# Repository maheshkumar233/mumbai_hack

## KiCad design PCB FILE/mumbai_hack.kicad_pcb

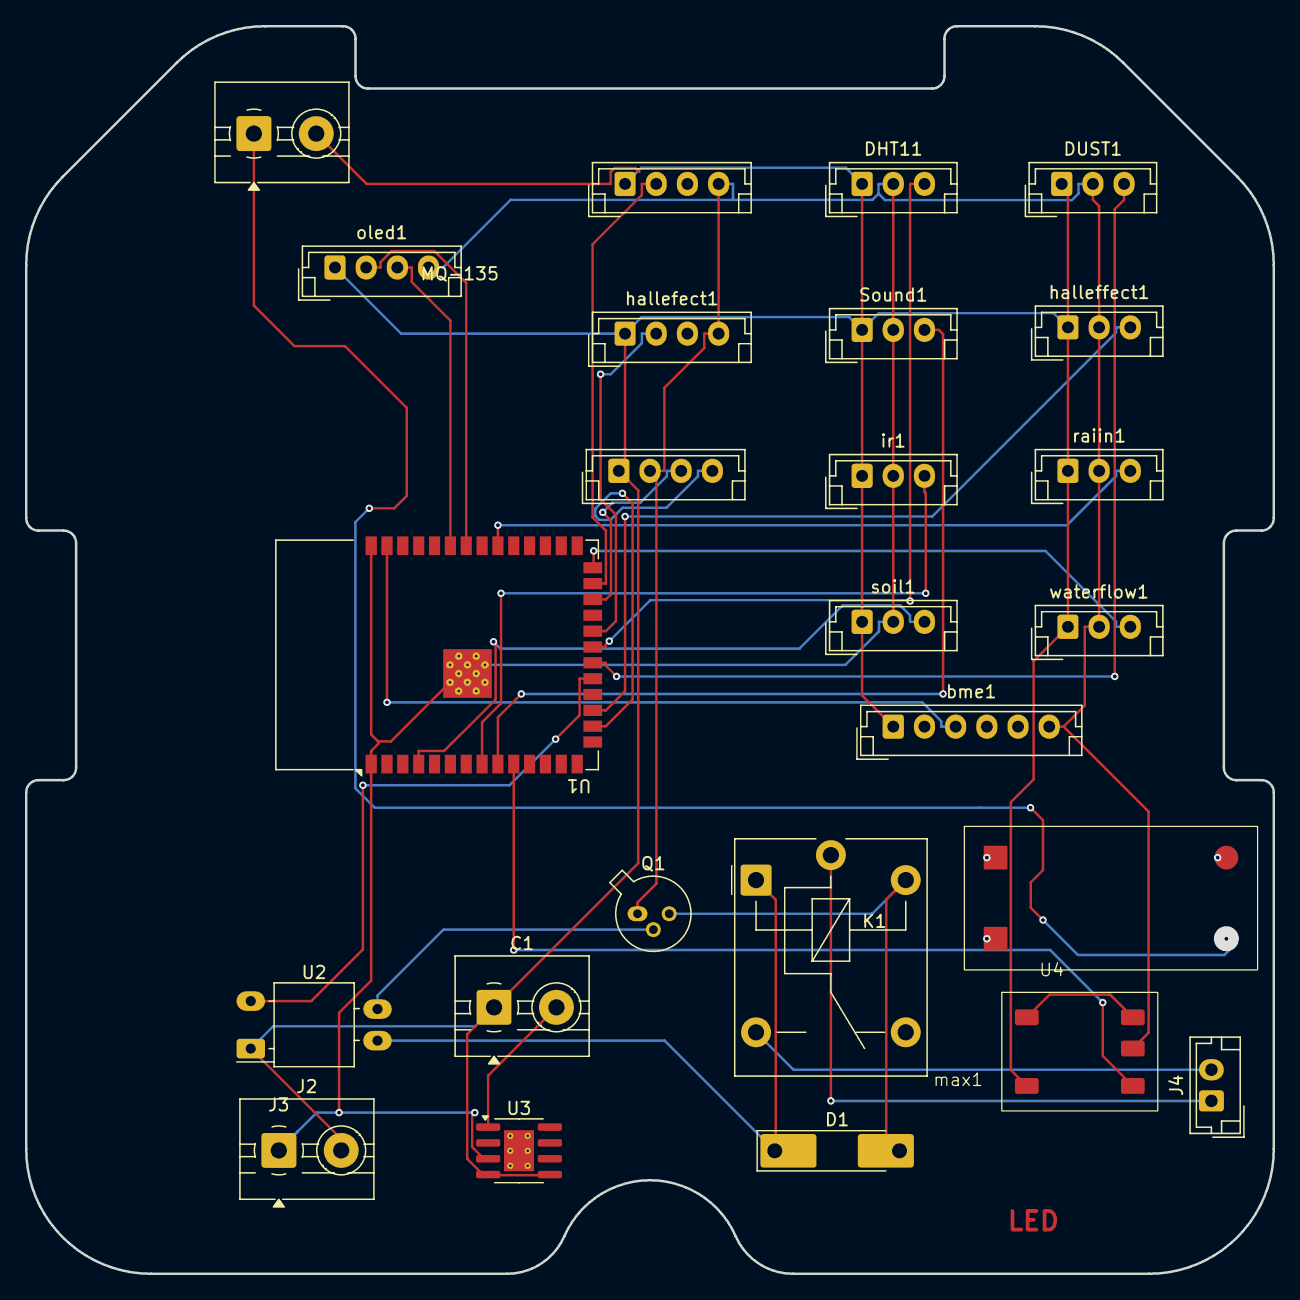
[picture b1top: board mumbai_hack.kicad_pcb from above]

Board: 2 copper layers, 100.0 x 100.0 mm, 25 parts (0 on the bottom side), 27 nets.

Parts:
C1: C; TerminalBlock_MaiXu_MX126-5.0-02P_1x02_P5.00mm
D1: D; D_MELF-RM10_Universal_Handsoldering
DHT11: JST_EH_B3B-EH-A_1x03_P2.50mm_Vertical
DUST1: JST_EH_B3B-EH-A_1x03_P2.50mm_Vertical
J2, J3: Conn_01x02_Pin; TerminalBlock_MaiXu_MX126-5.0-02P_1x02_P5.00mm
J4: Conn_01x02_Pin; JST_EH_B2B-EH-A_1x02_P2.50mm_Vertical
K1: FINDER-36.11; Relay_SPDT_Finder_36.11
MQ-135: JST_EH_B4B-EH-A_1x04_P2.50mm_Vertical
Q1: BC107; TO-18-3
Sound1: JST_EH_B3B-EH-A_1x03_P2.50mm_Vertical
U1: ESP32-S3-WROOM-1
U2: NSL-32; Luna_NSL-32
U3: TP4056-42-ESOP8; SOIC-8-1EP_3.9x4.9mm_P1.27mm_EP2.41x3.3mm_ThermalVias
U4: Untitled
bme1: JST_EH_B6B-EH-A_1x06_P2.50mm_Vertical
hallefect1: JST_EH_B4B-EH-A_1x04_P2.50mm_Vertical
halleffect1: JST_EH_B3B-EH-A_1x03_P2.50mm_Vertical
ir1: JST_EH_B3B-EH-A_1x03_P2.50mm_Vertical
max1: Untitled_1
oled1: JST_EH_B4B-EH-A_1x04_P2.50mm_Vertical
raiin1: JST_EH_B3B-EH-A_1x03_P2.50mm_Vertical
rtc1: JST_EH_B4B-EH-A_1x04_P2.50mm_Vertical
soil1: JST_EH_B3B-EH-A_1x03_P2.50mm_Vertical
waterflow1: JST_EH_B3B-EH-A_1x03_P2.50mm_Vertical

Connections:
26: U1.26 (IO45), waterflow1.3 (out)
GND: DHT11.2 (gnd), DUST1.2 (gnd), J2.1, MQ-135.4 (GND), Q1.1 (E), Sound1.2 (gnd), U1.1 (GND), U1.40 (GND), U1.41 (GND), U3.3 (GND), bme1.6 (Gnd), hallefect1.4 (GND), halleffect1.2 (gnd), ir1.2 (gnd), max1.4 (gnd), oled1.4 (GND), raiin1.2 (gnd), rtc1.2 (gnd), soil1.2 (gnd), waterflow1.2 (gnd)
unnamed: D1.2 (A), K1.A2, Q1.3 (C)
unnamed: D1.1 (K), K1.A1, U2.4 (R)
unnamed: DHT11.3 (out), U1.21 (IO13)
unnamed: C1.1, DHT11.1 (vcc), DUST1.1 (vcc), J2.2, MQ-135.1 (Vcc), Sound1.1 (vcc), U2.1 (A), U3.4 (V_{CC}), U3.5 (BAT), bme1.1 (Vcc), hallefect1.1 (Vcc), halleffect1.1 (vcc), ir1.1 (vcc), max1.2 (rs-), oled1.1 (vcc), raiin1.1 (vcc), rtc1.1 (vcc), soil1.1 (vcc), waterflow1.1 (vcc)
unnamed: DUST1.3 (out), U1.20 (IO12)
unnamed: J4.1, K1.11
unnamed: J4.2, K1.14
unnamed: MQ-135.2 (A0), U1.25 (IO48)
unnamed: Q1.2 (B), U2.3 (R)
unnamed: Sound1.3 (out), U1.9 (IO16)
unnamed: U1.27 (IO0), bme1.2 (SDA)
unnamed: U1.39 (IO1), bme1.3 (Scl)
unnamed: U1.19 (IO11), U2.2 (K)
unnamed: U1.22 (IO14), hallefect1.2 (A0)
unnamed: U1.8 (IO15), ir1.3 (out)
unnamed: U1.10 (IO17), max1.5 (out)
unnamed: U1.32 (IO39), raiin1.3 (out)
unnamed: U1.34 (IO41), oled1.2 (SDA)
unnamed: U1.35 (IO42), oled1.3 (SCL)
unnamed: U1.16 (IO46), rtc1.4 (data)
unnamed: U1.24 (IO47), rtc1.3 (clk)
unnamed: C1.2, U3.1 (TEMP)
unnamed: max1.1 (rs+), max1.3 (vcc)
h: U1.17 (IO9), halleffect1.3 (out)
so: U1.4 (IO4), soil1.3 (out)
